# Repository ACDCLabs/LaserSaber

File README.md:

# LaserSaber
Code for a Arduino based laser saber with a motion sensor and a sound chip

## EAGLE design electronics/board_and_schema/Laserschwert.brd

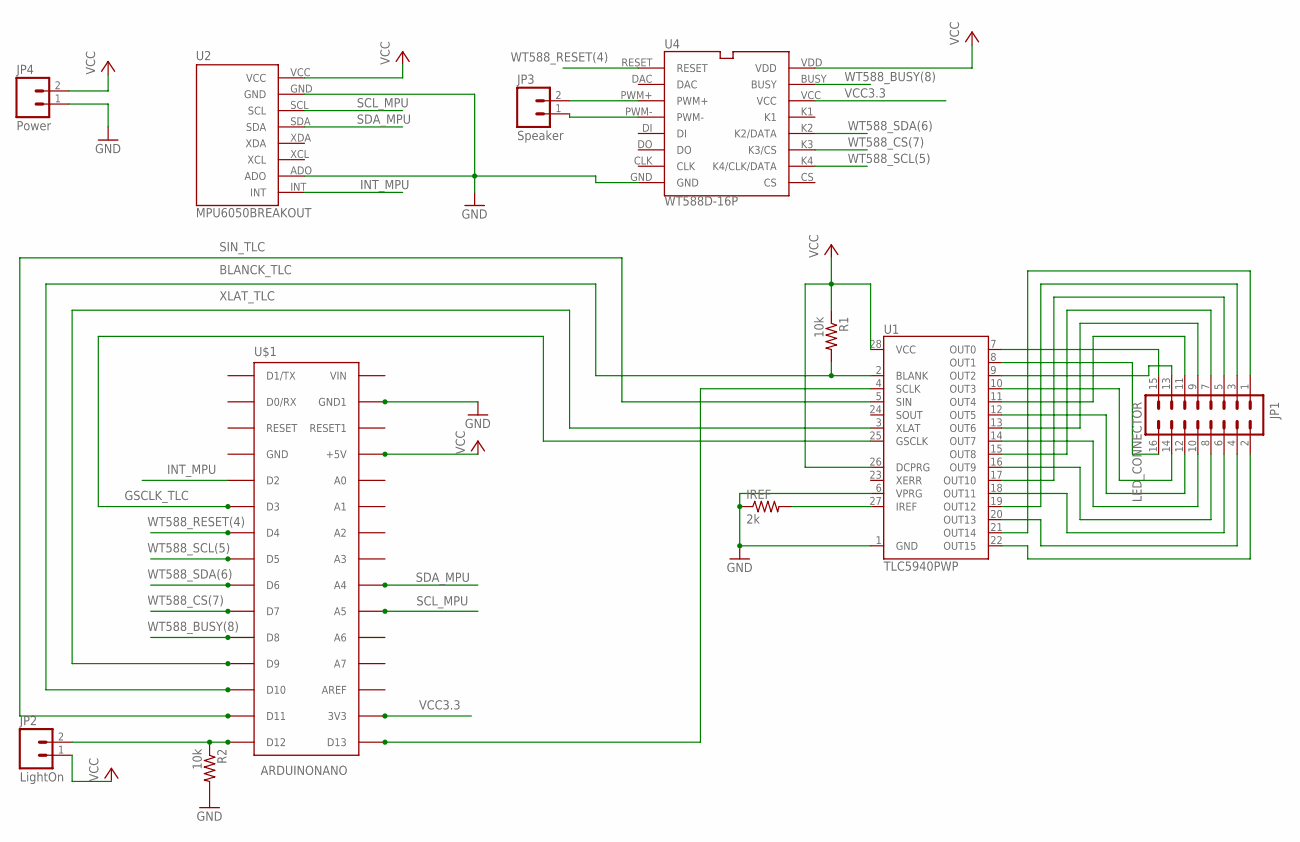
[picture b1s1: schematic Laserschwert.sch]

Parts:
IREF: 2k; 0805
JP1: LED_CONNECTOR; 2X8
JP2: LightOn; 1X02
JP3: Speaker; 1X02
JP4: Power; 1X02
R1, R2: 10k; 0805
U1: TLC5940PWP; TSSOP28-GROUNDPAD
U2: MPU6050BREAKOUT; PDIP-8
U4: WT588D-16P; PDIP-16
U$1: ARDUINONANO; PDIP-32

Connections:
BLANCK_TLC: R1.2, U1.2 (BLANK), U$1.D10
GND: IREF.1, JP4.1, R2.2, U1.1 (GND), U1.6 (VPRG), U2.ADO, U2.GND, U4.GND, U$1.GND1
GSCLK_TLC: U1.25 (GSCLK), U$1.D3
INT_MPU: U2.INT, U$1.D2
unnamed: JP1.15, U1.7 (OUT0)
unnamed: JP1.16, U1.8 (OUT1)
unnamed: JP1.13, U1.9 (OUT2)
unnamed: JP1.14, U1.10 (OUT3)
unnamed: JP1.11, U1.11 (OUT4)
unnamed: JP1.12, U1.12 (OUT5)
unnamed: JP1.9, U1.13 (OUT6)
unnamed: JP1.10, U1.14 (OUT7)
unnamed: JP1.7, U1.15 (OUT8)
unnamed: JP1.8, U1.16 (OUT9)
unnamed: JP1.5, U1.17 (OUT10)
unnamed: JP1.6, U1.18 (OUT11)
unnamed: JP1.3, U1.19 (OUT12)
unnamed: JP1.4, U1.20 (OUT13)
unnamed: JP1.1, U1.21 (OUT14)
unnamed: JP1.2, U1.22 (OUT15)
unnamed: JP2.2, R2.1, U$1.D12
unnamed: IREF.2, U1.27 (IREF)
unnamed: U1.4 (SCLK), U$1.D13
unnamed: JP3.2, U4.PWM+
unnamed: JP3.1, U4.PWM-
SCL_MPU: U2.SCL, U$1.A5
SDA_MPU: U2.SDA, U$1.A4
SIN_TLC: U1.5 (SIN), U$1.D11
VCC: JP2.1, JP4.2, R1.1, U1.26 (DCPRG), U1.28 (VCC), U2.VCC, U4.VDD, U$1.+5V
VCC3.3: U4.VCC, U$1.3V3
WT588_BUSY(8): U4.BUSY, U$1.D8
WT588_CS(7): U4.K3 (K3/CS), U$1.D7
WT588_RESET(4): U4.RESET, U$1.D4
WT588_SCL(5): U4.K4 (K4/CLK/DATA), U$1.D5
WT588_SDA(6): U4.K2 (K2/DATA), U$1.D6
XLAT_TLC: U1.3 (XLAT), U$1.D9

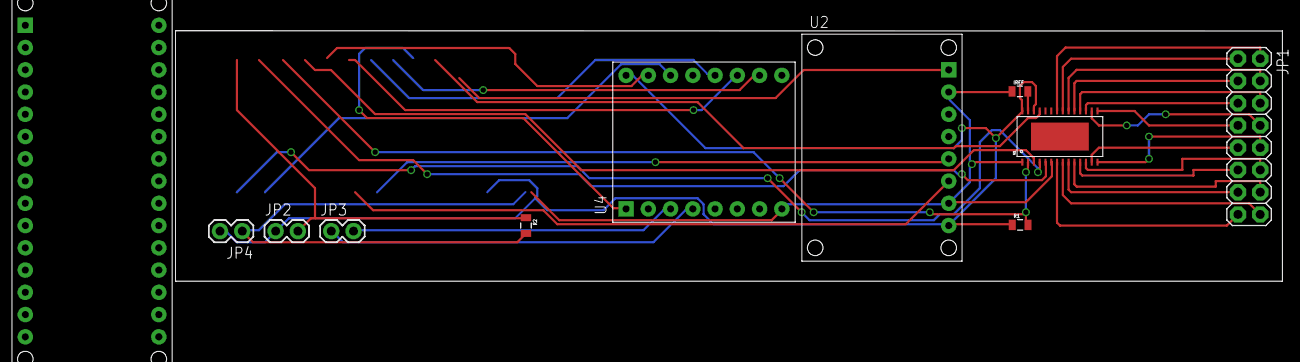
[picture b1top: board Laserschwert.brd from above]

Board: 2 copper layers, 126.4 x 28.6 mm, 11 parts (0 on the bottom side), 36 nets.

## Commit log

2016-05-20 Added eagle board and schema
2016-05-20 Added part list
2016-05-20 added a picture
2016-05-20 picture update
2016-05-20 minor change
2016-05-20 added sound files

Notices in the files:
parts and their libraries:
SparkFun-Connectors: Licensing: Creative Commons ShareAlike 4.0 International - https://creativecommons.org/licenses/by-sa/4.0
